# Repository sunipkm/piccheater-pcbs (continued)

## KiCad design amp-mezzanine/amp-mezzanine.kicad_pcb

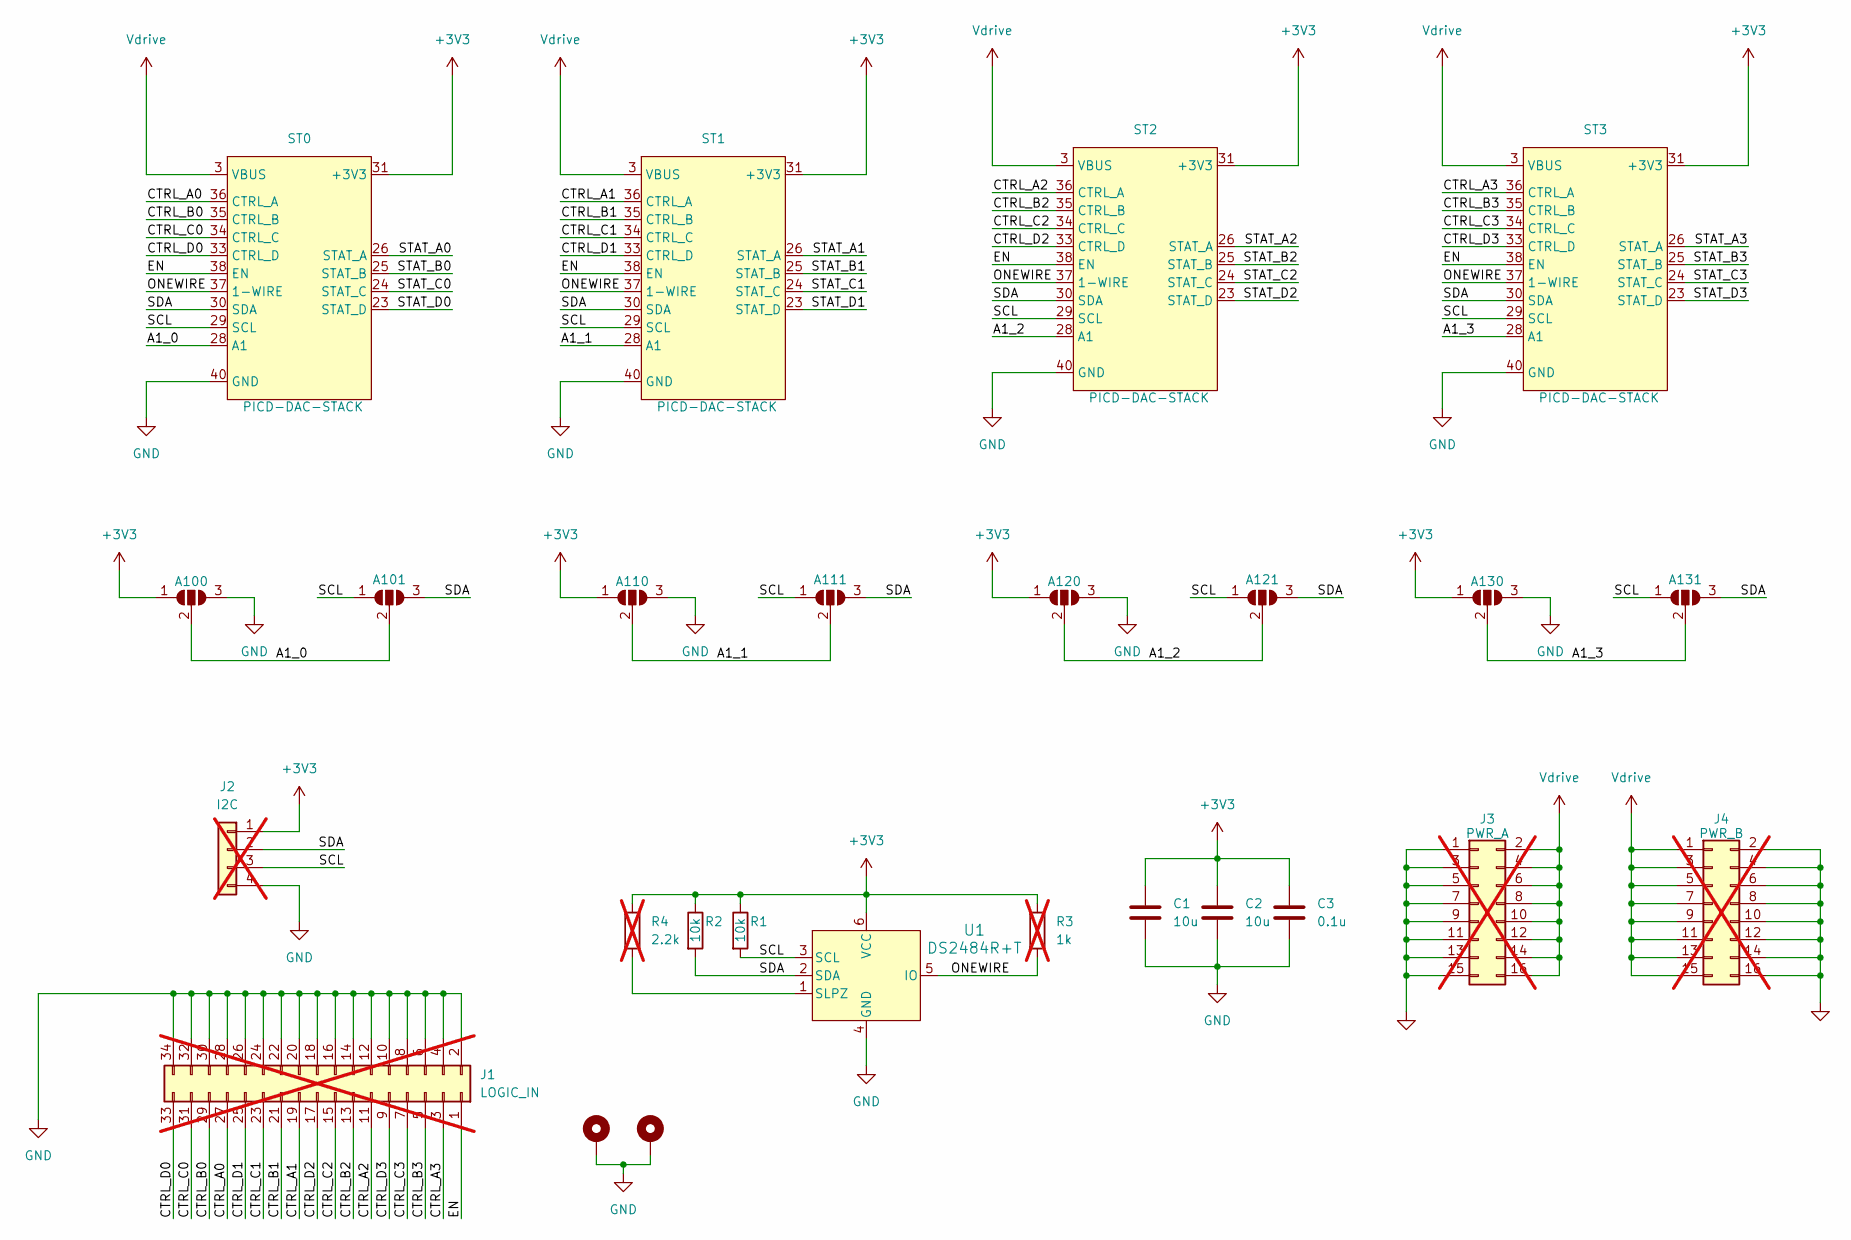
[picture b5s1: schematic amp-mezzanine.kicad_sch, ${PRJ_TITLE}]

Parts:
A100, A121: R; SolderJumper-3_P1.3mm_Open_RoundedPad1.0x1.5mm
A101, A111, A120, A130: NC; SolderJumper-3_P1.3mm_Open_RoundedPad1.0x1.5mm
A110, A131: L; SolderJumper-3_P1.3mm_Open_RoundedPad1.0x1.5mm
C1, C2: 10u; C_0805_2012Metric
C3: 0.1u; C_0805_2012Metric
H1, H2: MountingHole_Pad; MountingHole_3.2mm_M3_Pad_Via
J1: LOGIC_IN; PinHeader_2x17_P2.54mm_Vertical; not fitted
J2: I2C; PinHeader_1x04_P2.54mm_Vertical; not fitted
J3: PWR_A; PinHeader_2x08_P2.54mm_Vertical; not fitted
J4: PWR_B; PinHeader_2x08_P2.54mm_Vertical; not fitted
R1, R2: 10k; R_0402_1005Metric
R3: 1k; R_0402_1005Metric; not fitted
R4: 2.2k; R_0402_1005Metric; not fitted
ST0, ST1, ST2, ST3: PICD-DAC-STACK; PICCDAC-AMPHENOL-10132797-045100LF
U1: DS2484R+T; 21-0058I_MXM-L; Mfr # DS2484R+T; Mouser # 700-DS2484R+T

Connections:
+3V3: A100.1 (A), A110.1 (A), A120.1 (A), A130.1 (A), C1.1, C2.1, C3.1, J2.1, R1.1, R2.1, R3.1, R4.1, ST0.31 (+3V3), ST1.31 (+3V3), ST2.31 (+3V3), ST3.31 (+3V3), U1.6 (VCC)
/A1_0: A100.2 (C), A101.2 (C), ST0.28 (A1)
/A1_1: A110.2 (C), A111.2 (C), ST1.28 (A1)
/A1_2: A120.2 (C), A121.2 (C), ST2.28 (A1)
/A1_3: A130.2 (C), A131.2 (C), ST3.28 (A1)
/CTRL_A0: J1.27, ST0.36 (CTRL_A)
/CTRL_A1: J1.19, ST1.36 (CTRL_A)
/CTRL_A2: J1.11, ST2.36 (CTRL_A)
/CTRL_A3: J1.3, ST3.36 (CTRL_A)
/CTRL_B0: J1.29, ST0.35 (CTRL_B)
/CTRL_B1: J1.21, ST1.35 (CTRL_B)
/CTRL_B2: J1.13, ST2.35 (CTRL_B)
/CTRL_B3: J1.5, ST3.35 (CTRL_B)
/CTRL_C0: J1.31, ST0.34 (CTRL_C)
/CTRL_C1: J1.23, ST1.34 (CTRL_C)
/CTRL_C2: J1.15, ST2.34 (CTRL_C)
/CTRL_C3: J1.7, ST3.34 (CTRL_C)
/CTRL_D0: J1.33, ST0.33 (CTRL_D)
/CTRL_D1: J1.25, ST1.33 (CTRL_D)
/CTRL_D2: J1.17, ST2.33 (CTRL_D)
/CTRL_D3: J1.9, ST3.33 (CTRL_D)
/EN: J1.1, ST0.38 (EN), ST1.38 (EN), ST2.38 (EN), ST3.38 (EN)
/ONEWIRE: R3.2, ST0.37 (1-WIRE), ST1.37 (1-WIRE), ST2.37 (1-WIRE), ST3.37 (1-WIRE), U1.5 (IO)
/SCL: A101.1 (A), A111.1 (A), A121.1 (A), A131.1 (A), J2.3, R1.2, ST0.29 (SCL), ST1.29 (SCL), ST2.29 (SCL), ST3.29 (SCL), U1.3 (SCL)
/SDA: A101.3 (B), A111.3 (B), A121.3 (B), A131.3 (B), J2.2, R2.2, ST0.30 (SDA), ST1.30 (SDA), ST2.30 (SDA), ST3.30 (SDA), U1.2 (SDA)
/STAT_A0: ST0.26 (STAT_A)
/STAT_A1: ST1.26 (STAT_A)
/STAT_A2: ST2.26 (STAT_A)
/STAT_A3: ST3.26 (STAT_A)
/STAT_B0: ST0.25 (STAT_B)
/STAT_B1: ST1.25 (STAT_B)
/STAT_B2: ST2.25 (STAT_B)
/STAT_B3: ST3.25 (STAT_B)
/STAT_C0: ST0.24 (STAT_C)
/STAT_C1: ST1.24 (STAT_C)
/STAT_C2: ST2.24 (STAT_C)
/STAT_C3: ST3.24 (STAT_C)
/STAT_D0: ST0.23 (STAT_D)
/STAT_D1: ST1.23 (STAT_D)
/STAT_D2: ST2.23 (STAT_D)
/STAT_D3: ST3.23 (STAT_D)
GND: A100.3 (B), A110.3 (B), A120.3 (B), A130.3 (B), C1.2, C2.2, C3.2, H1.1, H2.1, J1.2, J1.4, J1.6, J1.8, J1.10, J1.12, J1.14, J1.16, J1.18, J1.20, J1.22, J1.24, J1.26, J1.28, J1.30, J1.32, J1.34, J2.4, J3.1, J3.3, J3.5, J3.7, J3.9, J3.11, J3.13, J3.15, J4.2, J4.4, J4.6, J4.8, J4.10, J4.12, J4.14, J4.16, ST0.1 (GND), ST0.2 (GND), ST0.19 (GND), ST0.20 (GND), ST0.21 (GND), ST0.22 (GND), ST0.27 (GND), ST0.32 (GND), ST0.39 (GND), ST0.40 (GND), ST0.MP (GND), ST1.1 (GND), ST1.2 (GND), ST1.19 (GND), ST1.20 (GND), ST1.21 (GND), ST1.22 (GND), ST1.27 (GND), ST1.32 (GND), ST1.39 (GND), ST1.40 (GND), ST1.MP (GND), ST2.1 (GND), ST2.2 (GND), ST2.19 (GND), ST2.20 (GND), ST2.21 (GND), ST2.22 (GND), ST2.27 (GND), ST2.32 (GND), ST2.39 (GND), ST2.40 (GND), ST2.MP (GND), ST3.1 (GND), ST3.2 (GND), ST3.19 (GND), ST3.20 (GND), ST3.21 (GND), ST3.22 (GND), ST3.27 (GND), ST3.32 (GND), ST3.39 (GND), ST3.40 (GND), ST3.MP (GND), U1.4 (GND)
unnamed: R4.2, U1.1 (SLPZ)
Vdrive: J3.2, J3.4, J3.6, J3.8, J3.10, J3.12, J3.14, J3.16, J4.1, J4.3, J4.5, J4.7, J4.9, J4.11, J4.13, J4.15, ST0.3 (VBUS), ST0.4 (VBUS), ST0.5 (VBUS), ST0.6 (VBUS), ST0.7 (VBUS), ST0.8 (VBUS), ST0.9 (VBUS), ST0.10 (VBUS), ST0.11 (VBUS), ST0.12 (VBUS), ST0.13 (VBUS), ST0.14 (VBUS), ST0.15 (VBUS), ST0.16 (VBUS), ST0.17 (VBUS), ST0.18 (VBUS), ST1.3 (VBUS), ST1.4 (VBUS), ST1.5 (VBUS), ST1.6 (VBUS), ST1.7 (VBUS), ST1.8 (VBUS), ST1.9 (VBUS), ST1.10 (VBUS), ST1.11 (VBUS), ST1.12 (VBUS), ST1.13 (VBUS), ST1.14 (VBUS), ST1.15 (VBUS), ST1.16 (VBUS), ST1.17 (VBUS), ST1.18 (VBUS), ST2.3 (VBUS), ST2.4 (VBUS), ST2.5 (VBUS), ST2.6 (VBUS), ST2.7 (VBUS), ST2.8 (VBUS), ST2.9 (VBUS), ST2.10 (VBUS), ST2.11 (VBUS), ST2.12 (VBUS), ST2.13 (VBUS), ST2.14 (VBUS), ST2.15 (VBUS), ST2.16 (VBUS), ST2.17 (VBUS), ST2.18 (VBUS), ST3.3 (VBUS), ST3.4 (VBUS), ST3.5 (VBUS), ST3.6 (VBUS), ST3.7 (VBUS), ST3.8 (VBUS), ST3.9 (VBUS), ST3.10 (VBUS), ST3.11 (VBUS), ST3.12 (VBUS), ST3.13 (VBUS), ST3.14 (VBUS), ST3.15 (VBUS), ST3.16 (VBUS), ST3.17 (VBUS), ST3.18 (VBUS)

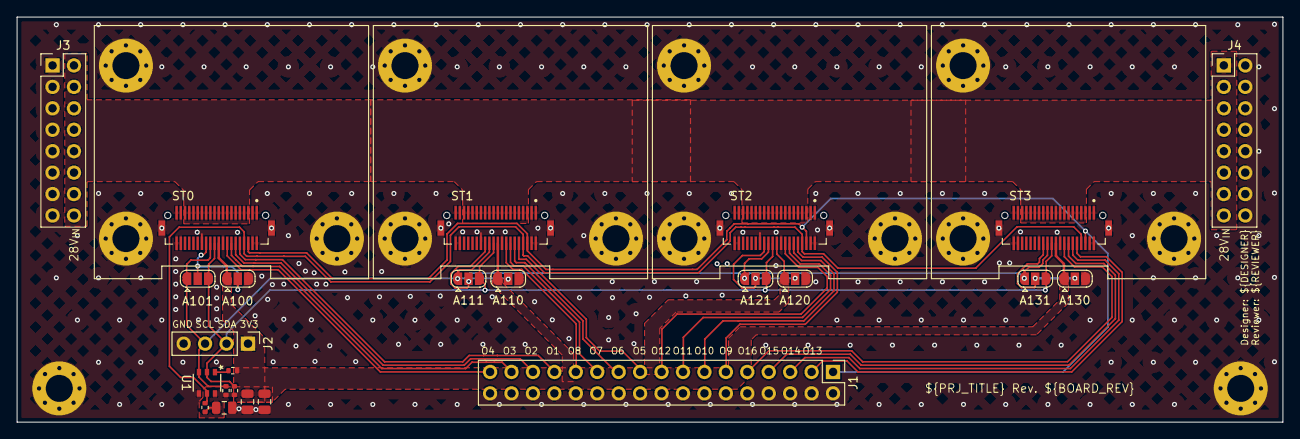
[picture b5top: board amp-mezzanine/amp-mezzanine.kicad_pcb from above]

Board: 2 copper layers, 150.0 x 48.0 mm, 26 parts (0 on the bottom side), 28 nets.

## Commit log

2025-12-05 Refactoring
2025-12-06 Added onewire temperature sensor
2025-12-06 Added DS2484 to mezzanine board
2025-12-07 Added FB smoothing capacitor to amp brd
2025-12-07 Adding DC-DC converter based system
2025-12-08 Modified DAC, AMP v2 and Mezzanine to support AMP v3. Finished AMP v3 design.
2025-12-08 Amp board v3 DRC
2025-12-08 Optimized temperature sensor from Kuravi's design, reworked inductor placement in amp board v3
2025-12-08 Final review with Joe
2026-02-12 Added math to schematic
2026-02-14 Added v4 board, early
2026-02-14 Added MCP19061 calculator
2026-02-17 Tested DAC and partially tested INA233
2026-02-17 Tested DAC and INA, doing new boards
2026-02-17 Updated mezannine v2
2026-02-18 Updated all boards for production
2026-02-24 Updated mezzanine v2 with Jason & Joe's comments
2026-02-24 Updated dac-brd connectors to vertical
2026-02-25 Updated amp-mezzanine: added test points
2026-02-25 Exported updated models
2026-02-25 Indicate using rp2350a. Re-wire I2C0 connections on DAC board for easier layout
2026-02-25 Removed PRL files from git
2026-02-28 Added part numbers
2026-02-28 Plotted gerbers
2026-03-02 Added readme and gitignore
2026-03-02 Adding power conditioning board
2026-03-03 Laid out inrush limiter
2026-03-04 Exported initial STEP files
